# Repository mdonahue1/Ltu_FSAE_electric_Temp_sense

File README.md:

# Ltu_FSAE_electric_Temp_sense
temp sense board I developed in my 3 semesters in the LTU FSAE Electric competition.

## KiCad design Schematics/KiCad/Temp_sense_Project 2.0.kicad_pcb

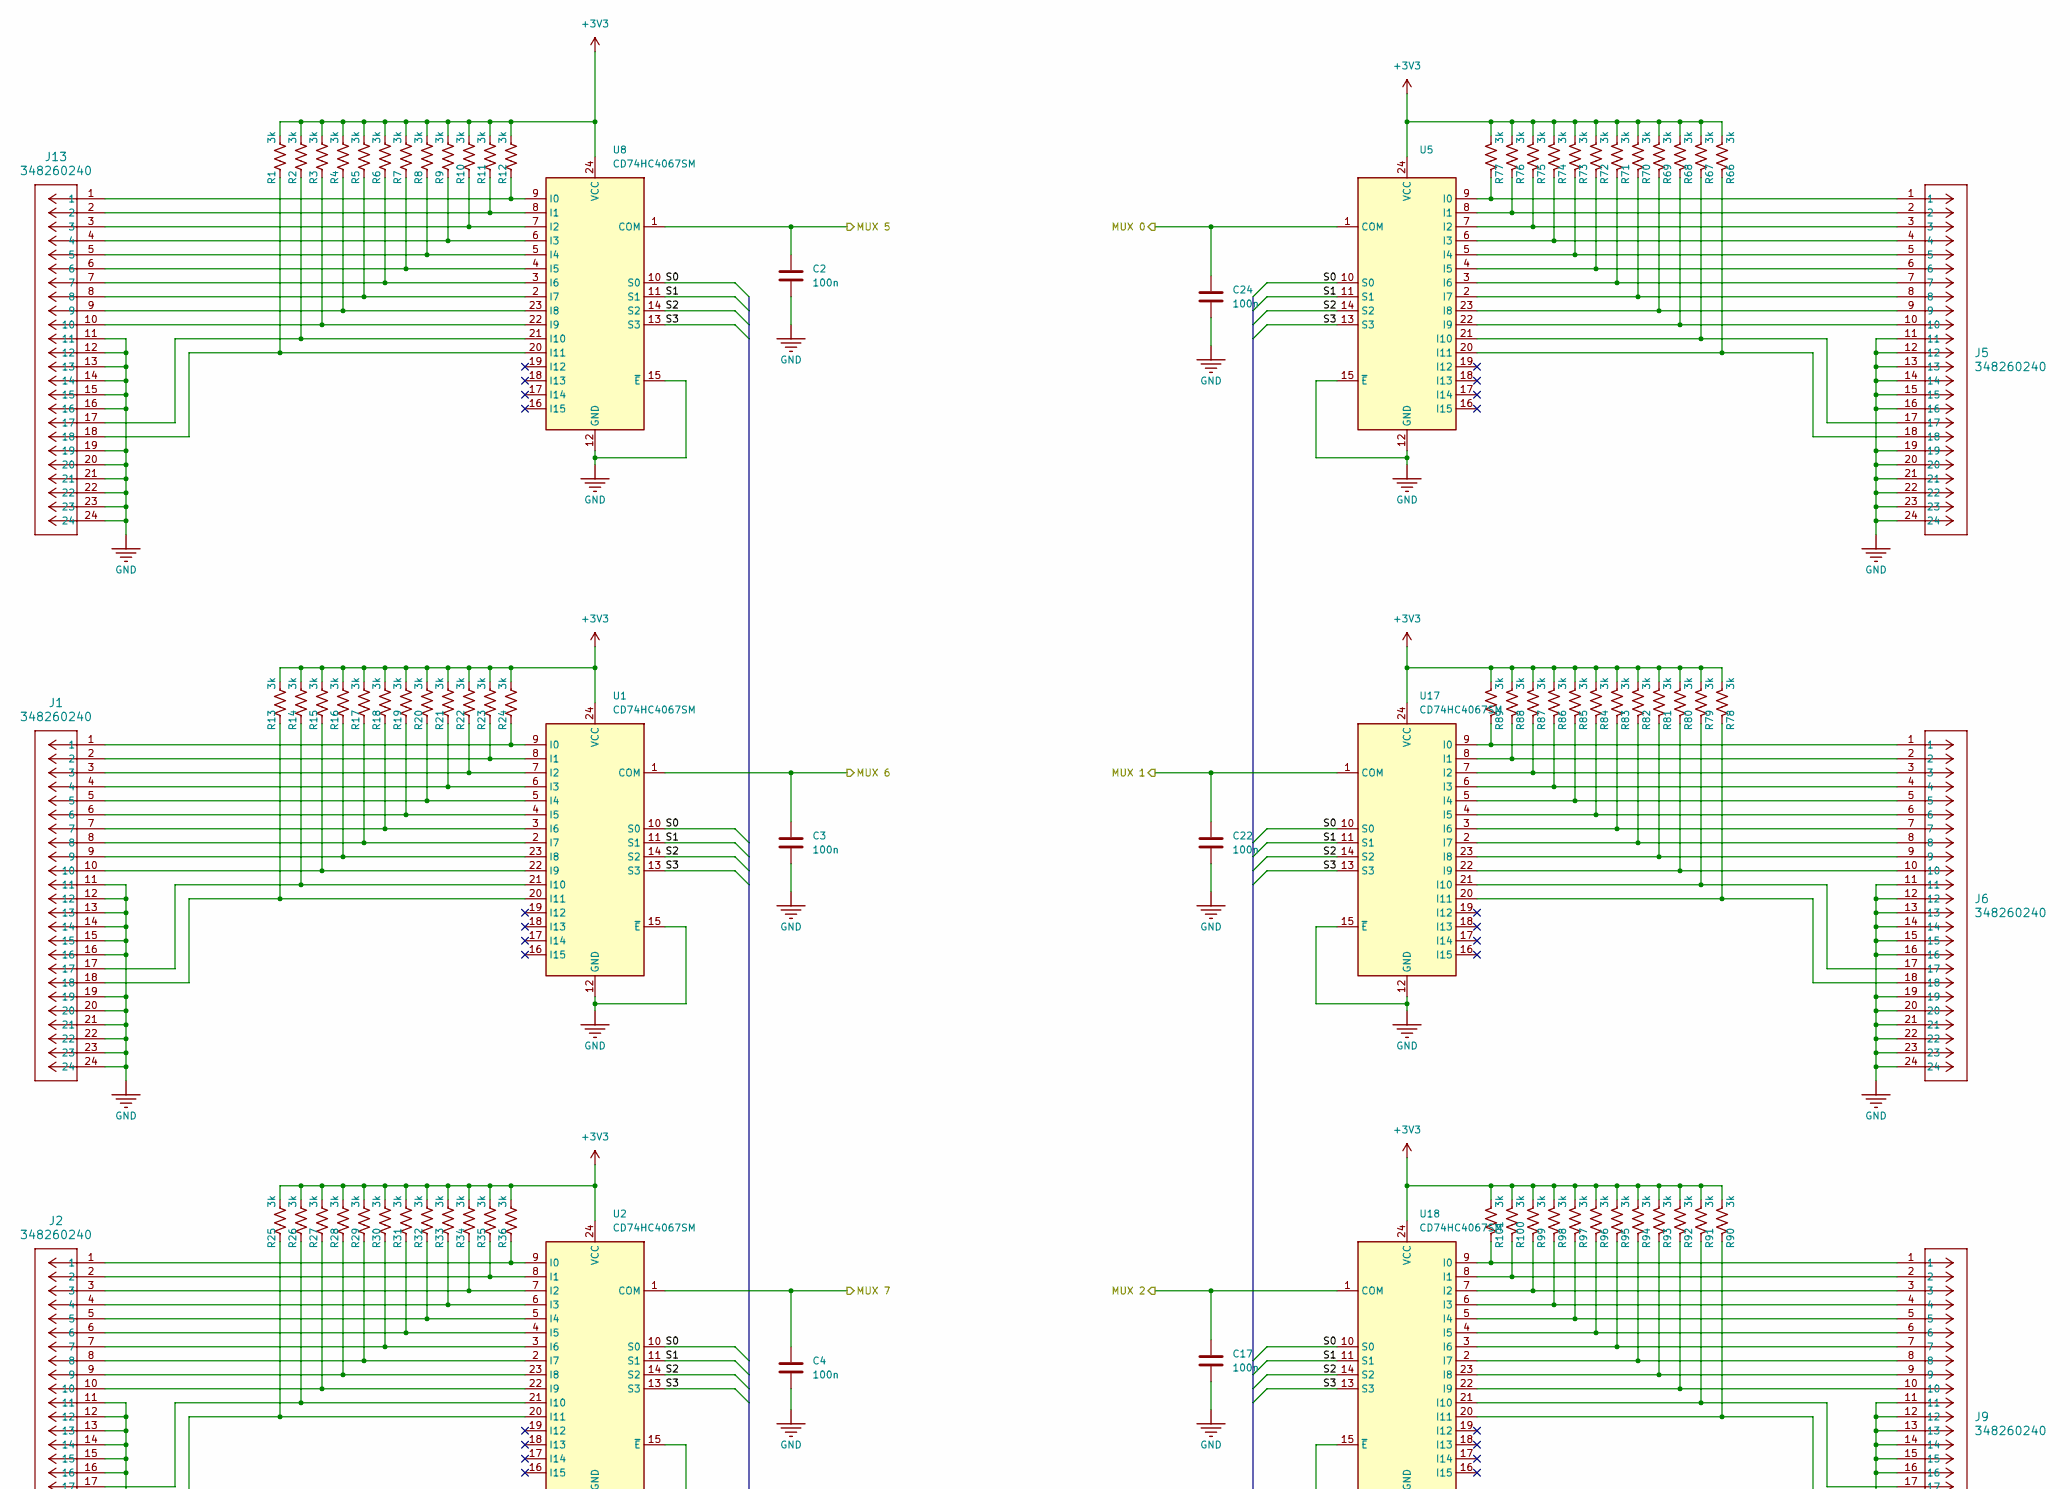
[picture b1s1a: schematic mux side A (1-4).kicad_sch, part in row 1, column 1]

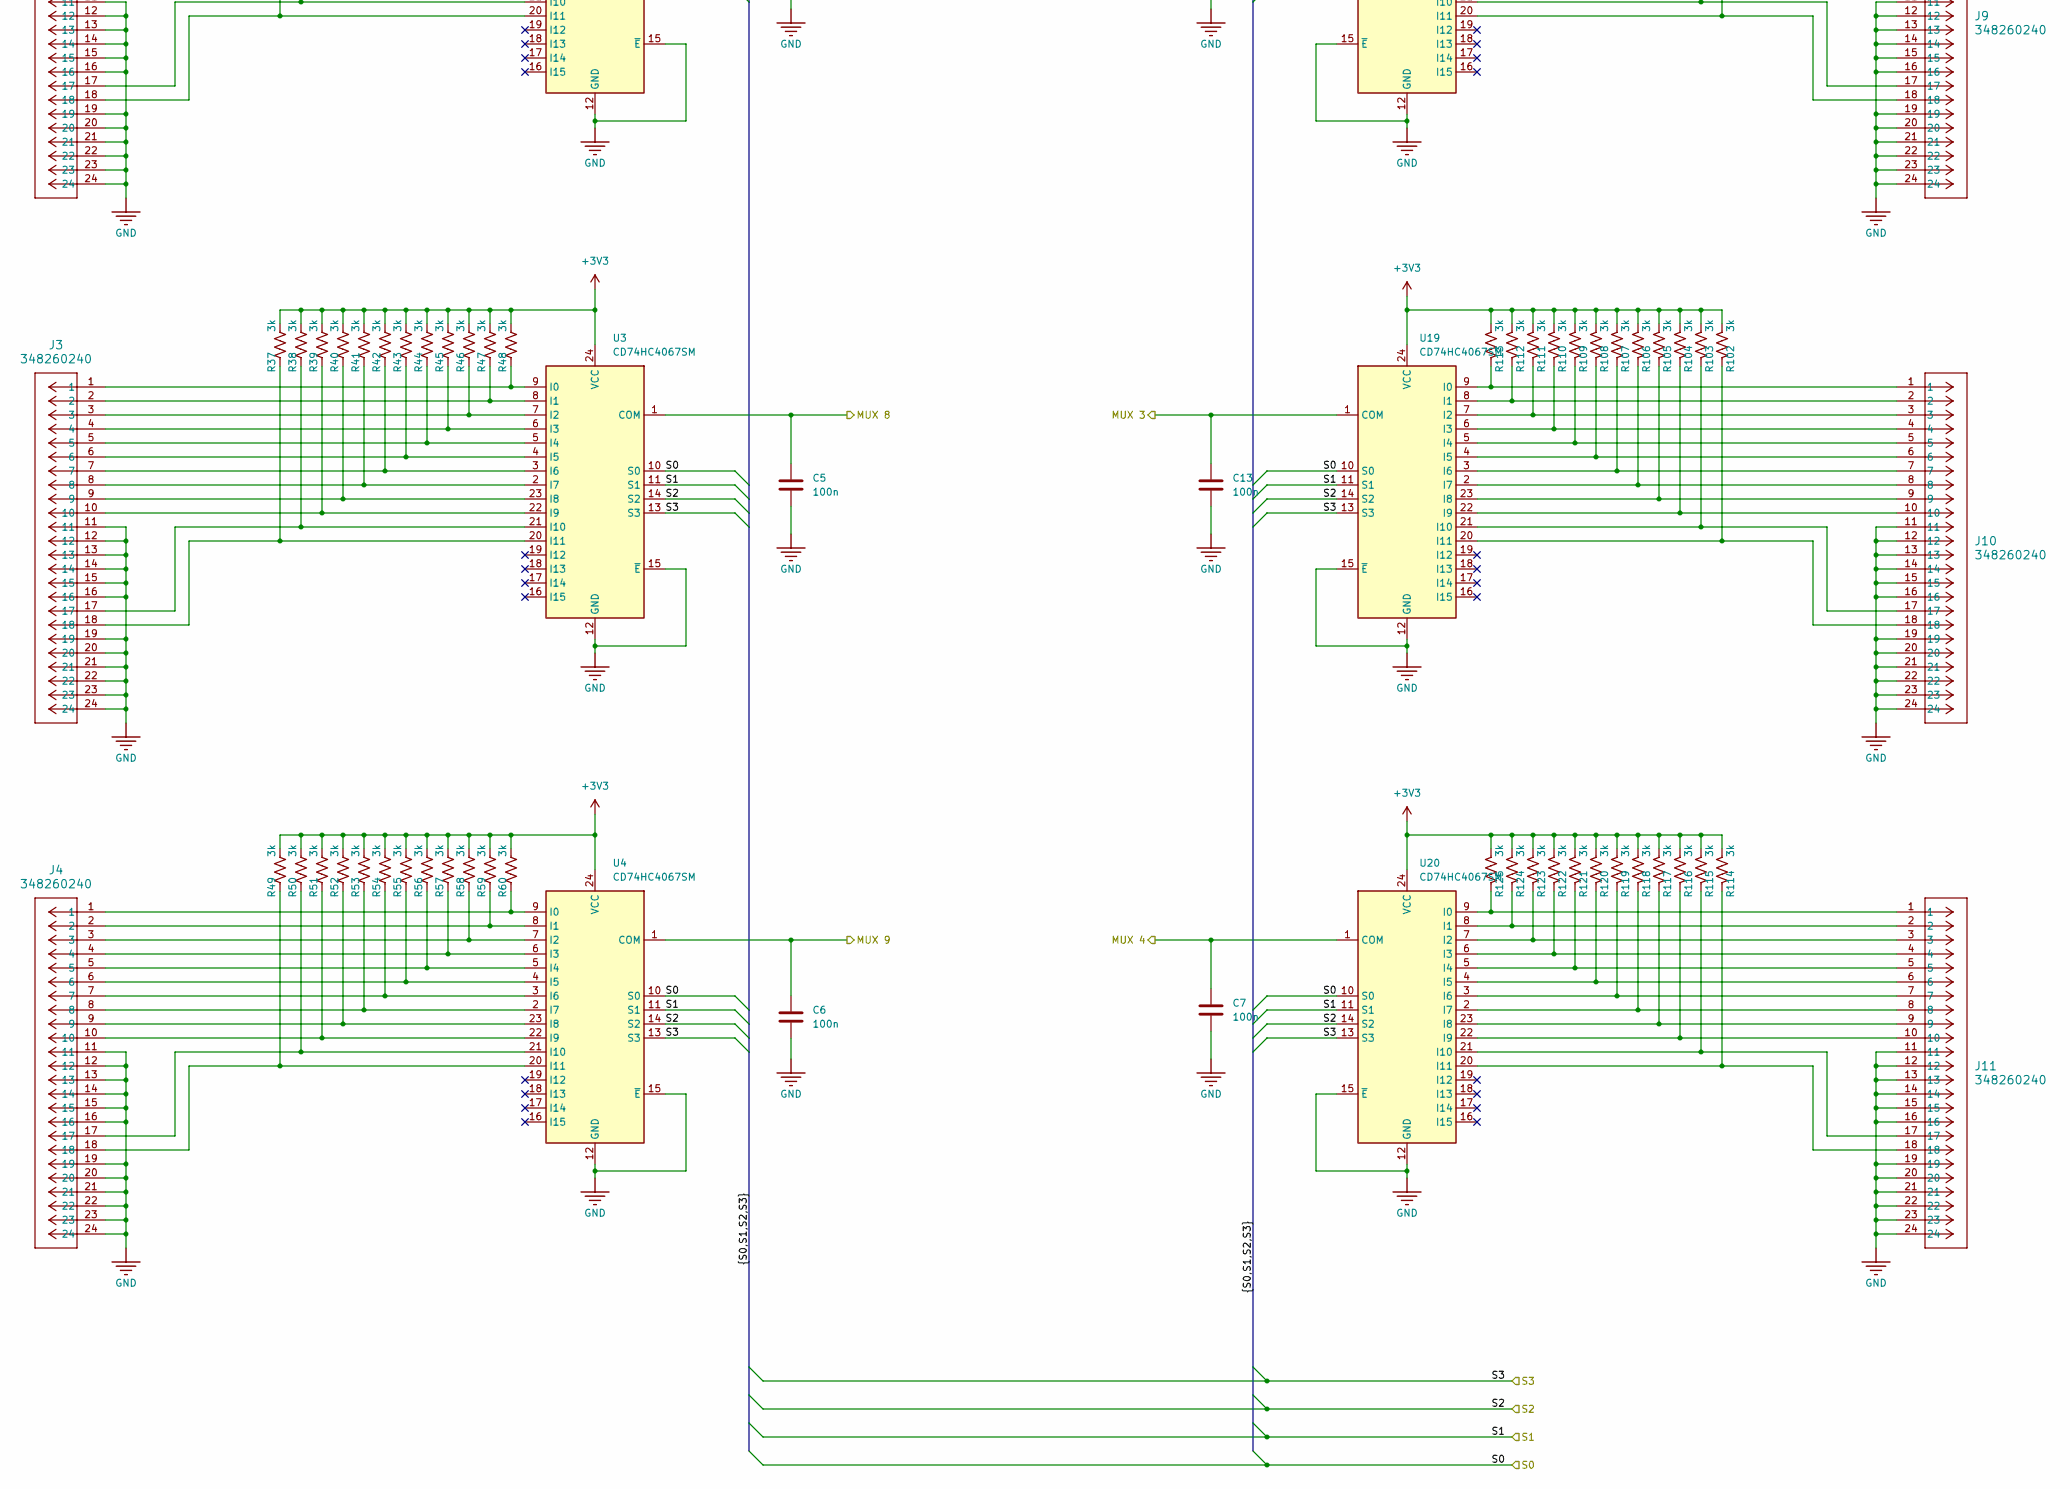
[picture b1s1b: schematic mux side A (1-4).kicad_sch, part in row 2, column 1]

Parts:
C2, C3, C4, C5, C6, C7, C13, C17, C22, C24: 100n; C_0603_1608Metric
J1, J2, J3, J4, J5, J6, J9, J10, J11, J13: 348260240; CONN_SD-34826-001_24_MOL
R1, R2, R3, R4, R5, R6, R7, R8, R9, R10, R11, R12, R13, R14, R15, R16, R17, R18, R19, R20, R21, R22, R23, R24, R25, R26, R27, R28, R29, R30, R31, R32, R33, R34, R35, R36, R37, R38, R39, R40, R41, R42, R43, R44, R45, R46, R47, R48, R49, R50, R51, R52, R53, R54, R55, R56, R57, R58, R59, R60, R66, R67, R68, R69, R70, R71, R72, R73, R74, R75, R76, R77, R78, R79, R80, R81, R82, R83, R84, R85, R86, R87, R88, R89, R90, R91, R92, R93, R94, R95, R96, R97, R98, R99, R100, R101, R102, R103, R104, R105, R106, R107, R108, R109, R110, R111, R112, R113, R114, R115, R116, R117, R118, R119, R120, R121, R122, R123, R124, R125: 3k; R_0603_1608Metric
U1, U2, U3, U4, U5, U8, U17, U18, U19, U20: CD74HC4067SM; SSOP-24_5.3x8.2mm_P0.65mm

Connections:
+3V3: R1.1, R2.1, R3.1, R4.1, R5.1, R6.1, R7.1, R8.1, R9.1, R10.1, R11.1, R12.1, R13.1, R14.1, R15.1, R16.1, R17.1, R18.1, R19.1, R20.1, R21.1, R22.1, R23.1, R24.1, R25.1, R26.1, R27.1, R28.1, R29.1, R30.1, R31.1, R32.1, R33.1, R34.1, R35.1, R36.1, R37.1, R38.1, R39.1, R40.1, R41.1, R42.1, R43.1, R44.1, R45.1, R46.1, R47.1, R48.1, R49.1, R50.1, R51.1, R52.1, R53.1, R54.1, R55.1, R56.1, R57.1, R58.1, R59.1, R60.1, R66.1, R67.1, R68.1, R69.1, R70.1, R71.1, R72.1, R73.1, R74.1, R75.1, R76.1, R77.1, R78.1, R79.1, R80.1, R81.1, R82.1, R83.1, R84.1, R85.1, R86.1, R87.1, R88.1, R89.1, R90.1, R91.1, R92.1, R93.1, R94.1, R95.1, R96.1, R97.1, R98.1, R99.1, R100.1, R101.1, R102.1, R103.1, R104.1, R105.1, R106.1, R107.1, R108.1, R109.1, R110.1, R111.1, R112.1, R113.1, R114.1, R115.1, R116.1, R117.1, R118.1, R119.1, R120.1, R121.1, R122.1, R123.1, R124.1, R125.1, U1.24 (VCC), U2.24 (VCC), U3.24 (VCC), U4.24 (VCC), U5.24 (VCC), U8.24 (VCC), U17.24 (VCC), U18.24 (VCC), U19.24 (VCC), U20.24 (VCC); also elsewhere on the board
/MCU/MUX 0: C24.1, U5.1 (COM); also elsewhere on the board
/MCU/MUX 1: C22.1, U17.1 (COM); also elsewhere on the board
/MCU/MUX 2: C17.1, U18.1 (COM); also elsewhere on the board
/MCU/MUX 3: C13.1, U19.1 (COM); also elsewhere on the board
/MCU/MUX 4: C7.1, U20.1 (COM); also elsewhere on the board
/MCU/MUX 5: C2.1, U8.1 (COM); also elsewhere on the board
/MCU/MUX 6: C3.1, U1.1 (COM); also elsewhere on the board
/MCU/MUX 7: C4.1, U2.1 (COM); also elsewhere on the board
/MCU/MUX 8: C5.1, U3.1 (COM); also elsewhere on the board
/MCU/MUX 9: C6.1, U4.1 (COM); also elsewhere on the board
/MCU/S0: U1.10 (S0), U2.10 (S0), U3.10 (S0), U4.10 (S0), U5.10 (S0), U8.10 (S0), U17.10 (S0), U18.10 (S0), U19.10 (S0), U20.10 (S0); also elsewhere on the board
/MCU/S1: U1.11 (S1), U2.11 (S1), U3.11 (S1), U4.11 (S1), U5.11 (S1), U8.11 (S1), U17.11 (S1), U18.11 (S1), U19.11 (S1), U20.11 (S1); also elsewhere on the board
/MCU/S2: U1.14 (S2), U2.14 (S2), U3.14 (S2), U4.14 (S2), U5.14 (S2), U8.14 (S2), U17.14 (S2), U18.14 (S2), U19.14 (S2), U20.14 (S2); also elsewhere on the board
/MCU/S3: U1.13 (S3), U2.13 (S3), U3.13 (S3), U4.13 (S3), U5.13 (S3), U8.13 (S3), U17.13 (S3), U18.13 (S3), U19.13 (S3), U20.13 (S3); also elsewhere on the board
GND: C2.2, C3.2, C4.2, C5.2, C6.2, C7.2, C13.2, C17.2, C22.2, C24.2, J1.11, J1.12, J1.13, J1.14, J1.15, J1.16, J1.19, J1.20, J1.21, J1.22, J1.23, J1.24, J2.11, J2.12, J2.13, J2.14, J2.15, J2.16, J2.19, J2.20, J2.21, J2.22, J2.23, J2.24, J3.11, J3.12, J3.13, J3.14, J3.15, J3.16, J3.19, J3.20, J3.21, J3.22, J3.23, J3.24, J4.11, J4.12, J4.13, J4.14, J4.15, J4.16, J4.19, J4.20, J4.21, J4.22, J4.23, J4.24, J5.11, J5.12, J5.13, J5.14, J5.15, J5.16, J5.19, J5.20, J5.21, J5.22, J5.23, J5.24, J6.11, J6.12, J6.13, J6.14, J6.15, J6.16, J6.19, J6.20, J6.21, J6.22, J6.23, J6.24, J9.11, J9.12, J9.13, J9.14, J9.15, J9.16, J9.19, J9.20, J9.21, J9.22, J9.23, J9.24, J10.11, J10.12, J10.13, J10.14, J10.15, J10.16, J10.19, J10.20, J10.21, J10.22, J10.23, J10.24, J11.11, J11.12, J11.13, J11.14, J11.15, J11.16, J11.19, J11.20, J11.21, J11.22, J11.23, J11.24, J13.11, J13.12, J13.13, J13.14, J13.15, J13.16, J13.19, J13.20, J13.21, J13.22, J13.23, J13.24, U1.12 (GND), U1.15 (~E), U2.12 (GND), U2.15 (~E), U3.12 (GND), U3.15 (~E), U4.12 (GND), U4.15 (~E), U5.12 (GND), U5.15 (~E), U8.12 (GND), U8.15 (~E), U17.12 (GND), U17.15 (~E), U18.12 (GND), U18.15 (~E), U19.12 (GND), U19.15 (~E), U20.12 (GND), U20.15 (~E); also elsewhere on the board
unnamed: J1.1, R24.2, U1.9 (I0)
unnamed: J1.2, R23.2, U1.8 (I1)
unnamed: J1.3, R22.2, U1.7 (I2)
unnamed: J1.4, R21.2, U1.6 (I3)
unnamed: J1.5, R20.2, U1.5 (I4)
unnamed: J1.6, R19.2, U1.4 (I5)
unnamed: J1.7, R18.2, U1.3 (I6)
unnamed: J1.8, R17.2, U1.2 (I7)
unnamed: J1.9, R16.2, U1.23 (I8)
unnamed: J1.10, R15.2, U1.22 (I9)
unnamed: J1.17, R14.2, U1.21 (I10)
unnamed: J1.18, R13.2, U1.20 (I11)
unnamed: J2.1, R36.2, U2.9 (I0)
unnamed: J2.2, R35.2, U2.8 (I1)
unnamed: J2.3, R34.2, U2.7 (I2)
unnamed: J2.4, R33.2, U2.6 (I3)
unnamed: J2.5, R32.2, U2.5 (I4)
unnamed: J2.6, R31.2, U2.4 (I5)
unnamed: J2.7, R30.2, U2.3 (I6)
unnamed: J2.8, R29.2, U2.2 (I7)
unnamed: J2.9, R28.2, U2.23 (I8)
unnamed: J2.10, R27.2, U2.22 (I9)
unnamed: J2.17, R26.2, U2.21 (I10)
unnamed: J2.18, R25.2, U2.20 (I11)
unnamed: J3.1, R48.2, U3.9 (I0)
unnamed: J3.2, R47.2, U3.8 (I1)
unnamed: J3.3, R46.2, U3.7 (I2)
unnamed: J3.4, R45.2, U3.6 (I3)
unnamed: J3.5, R44.2, U3.5 (I4)
unnamed: J3.6, R43.2, U3.4 (I5)
unnamed: J3.7, R42.2, U3.3 (I6)
unnamed: J3.8, R41.2, U3.2 (I7)
unnamed: J3.9, R40.2, U3.23 (I8)
unnamed: J3.10, R39.2, U3.22 (I9)
unnamed: J3.17, R38.2, U3.21 (I10)
unnamed: J3.18, R37.2, U3.20 (I11)
unnamed: J4.1, R60.2, U4.9 (I0)
unnamed: J4.2, R59.2, U4.8 (I1)
unnamed: J4.3, R58.2, U4.7 (I2)
unnamed: J4.4, R57.2, U4.6 (I3)
unnamed: J4.5, R56.2, U4.5 (I4)
unnamed: J4.6, R55.2, U4.4 (I5)
unnamed: J4.7, R54.2, U4.3 (I6)
unnamed: J4.8, R53.2, U4.2 (I7)
unnamed: J4.9, R52.2, U4.23 (I8)
unnamed: J4.10, R51.2, U4.22 (I9)
unnamed: J4.17, R50.2, U4.21 (I10)
unnamed: J4.18, R49.2, U4.20 (I11)
unnamed: J5.1, R77.2, U5.9 (I0)
unnamed: J5.2, R76.2, U5.8 (I1)
unnamed: J5.3, R75.2, U5.7 (I2)
unnamed: J5.4, R74.2, U5.6 (I3)
unnamed: J5.5, R73.2, U5.5 (I4)
unnamed: J5.6, R72.2, U5.4 (I5)
unnamed: J5.7, R71.2, U5.3 (I6)
unnamed: J5.8, R70.2, U5.2 (I7)
unnamed: J5.9, R69.2, U5.23 (I8)
unnamed: J5.10, R68.2, U5.22 (I9)
unnamed: J5.17, R67.2, U5.21 (I10)
unnamed: J5.18, R66.2, U5.20 (I11)
unnamed: J13.1, R12.2, U8.9 (I0)
unnamed: J13.2, R11.2, U8.8 (I1)
unnamed: J13.3, R10.2, U8.7 (I2)
unnamed: J13.4, R9.2, U8.6 (I3)
unnamed: J13.5, R8.2, U8.5 (I4)
unnamed: J13.6, R7.2, U8.4 (I5)
unnamed: J13.7, R6.2, U8.3 (I6)
unnamed: J13.8, R5.2, U8.2 (I7)
unnamed: J13.9, R4.2, U8.23 (I8)
unnamed: J13.10, R3.2, U8.22 (I9)
unnamed: J13.17, R2.2, U8.21 (I10)
unnamed: J13.18, R1.2, U8.20 (I11)
unnamed: J6.1, R89.2, U17.9 (I0)
unnamed: J6.2, R88.2, U17.8 (I1)
unnamed: J6.3, R87.2, U17.7 (I2)
unnamed: J6.4, R86.2, U17.6 (I3)
unnamed: J6.5, R85.2, U17.5 (I4)
unnamed: J6.6, R84.2, U17.4 (I5)
unnamed: J6.7, R83.2, U17.3 (I6)
unnamed: J6.8, R82.2, U17.2 (I7)
unnamed: J6.9, R81.2, U17.23 (I8)
unnamed: J6.10, R80.2, U17.22 (I9)
unnamed: J6.17, R79.2, U17.21 (I10)
unnamed: J6.18, R78.2, U17.20 (I11)
unnamed: J9.1, R101.2, U18.9 (I0)
unnamed: J9.2, R100.2, U18.8 (I1)
unnamed: J9.3, R99.2, U18.7 (I2)
unnamed: J9.4, R98.2, U18.6 (I3)
unnamed: J9.5, R97.2, U18.5 (I4)
unnamed: J9.6, R96.2, U18.4 (I5)
unnamed: J9.7, R95.2, U18.3 (I6)
unnamed: J9.8, R94.2, U18.2 (I7)
unnamed: J9.9, R93.2, U18.23 (I8)
unnamed: J9.10, R92.2, U18.22 (I9)
unnamed: J9.17, R91.2, U18.21 (I10)
unnamed: J9.18, R90.2, U18.20 (I11)
unnamed: J10.1, R113.2, U19.9 (I0)
unnamed: J10.2, R112.2, U19.8 (I1)
unnamed: J10.3, R111.2, U19.7 (I2)
unnamed: J10.4, R110.2, U19.6 (I3)
unnamed: J10.5, R109.2, U19.5 (I4)
unnamed: J10.6, R108.2, U19.4 (I5)
unnamed: J10.7, R107.2, U19.3 (I6)
unnamed: J10.8, R106.2, U19.2 (I7)
unnamed: J10.9, R105.2, U19.23 (I8)
unnamed: J10.10, R104.2, U19.22 (I9)
unnamed: J10.17, R103.2, U19.21 (I10)
unnamed: J10.18, R102.2, U19.20 (I11)
unnamed: J11.1, R125.2, U20.9 (I0)
unnamed: J11.2, R124.2, U20.8 (I1)
unnamed: J11.3, R123.2, U20.7 (I2)
unnamed: J11.4, R122.2, U20.6 (I3)
unnamed: J11.5, R121.2, U20.5 (I4)
unnamed: J11.6, R120.2, U20.4 (I5)
unnamed: J11.7, R119.2, U20.3 (I6)
unnamed: J11.8, R118.2, U20.2 (I7)
unnamed: J11.9, R117.2, U20.23 (I8)
unnamed: J11.10, R116.2, U20.22 (I9)
unnamed: J11.17, R115.2, U20.21 (I10)
unnamed: J11.18, R114.2, U20.20 (I11)

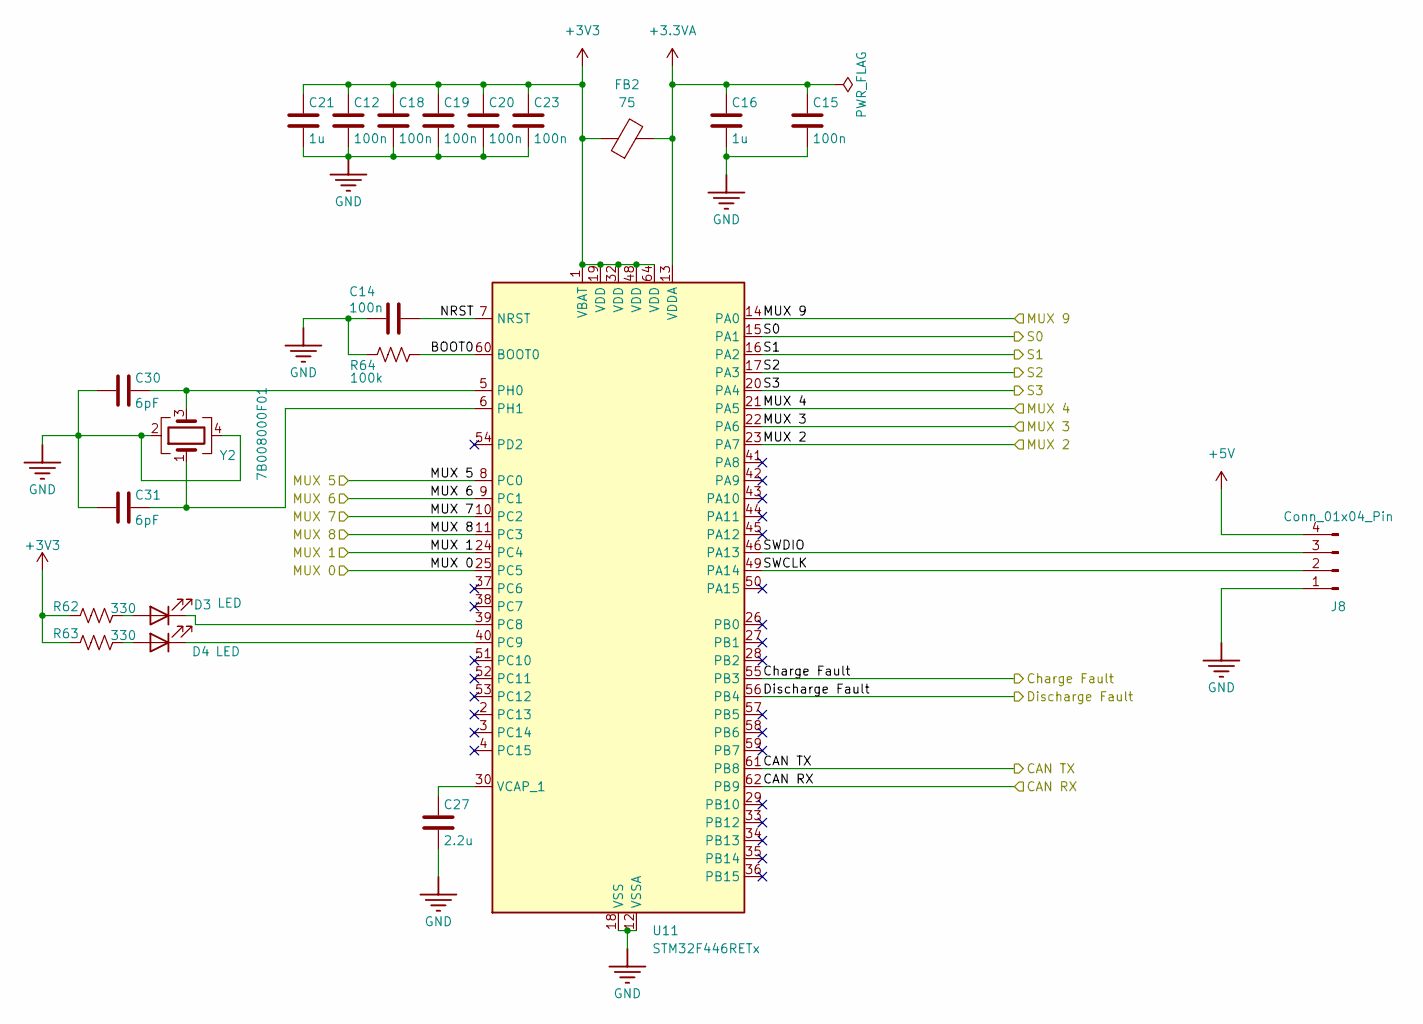
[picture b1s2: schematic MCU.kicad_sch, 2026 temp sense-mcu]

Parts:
C12, C14, C15, C18, C19, C20, C23: 100n; C_0603_1608Metric
C16, C21: 1u; C_0603_1608Metric
C27: 2.2u; C_0603_1608Metric
C30, C31: 6pF; C_0402_1005Metric; MPN GJM1555C1H6R0CB01D; JLCPCB Part # C161330
D3, D4: LED; LED_0603_1608Metric
FB2: 75; R_0603_1608Metric
J8: Conn_01x04_Pin; PinHeader_1x04_P2.54mm_Vertical
R62, R63: 330; R_0603_1608Metric
R64: 100k; R_0603_1608Metric
U11: STM32F446RETx; LQFP-64_10x10mm_P0.5mm
Y2: 7B008000F01; Crystal_SMD_3225-4Pin_3.2x2.5mm; MPN 7B008000F01; JLCPCB Part # C648984

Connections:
+3.3VA: C15.1, C16.1, FB2.2, U11.13 (VDDA)
+3V3: C12.1, C18.1, C19.1, C20.1, C21.1, C23.1, FB2.1, R62.1, R63.1, U11.1 (VBAT), U11.19 (VDD), U11.32 (VDD), U11.48 (VDD), U11.64 (VDD); also elsewhere on the board
+5V: J8.4; also elsewhere on the board
/MCU/BOOT0: R64.1, U11.60 (BOOT0)
/MCU/CAN RX: U11.62 (PB9); also elsewhere on the board
/MCU/CAN TX: U11.61 (PB8); also elsewhere on the board
/MCU/Charge Fault: U11.55 (PB3); also elsewhere on the board
/MCU/Discharge Fault: U11.56 (PB4); also elsewhere on the board
/MCU/MUX 0: U11.25 (PC5); also elsewhere on the board
/MCU/MUX 1: U11.24 (PC4); also elsewhere on the board
/MCU/MUX 2: U11.23 (PA7); also elsewhere on the board
/MCU/MUX 3: U11.22 (PA6); also elsewhere on the board
/MCU/MUX 4: U11.21 (PA5); also elsewhere on the board
/MCU/MUX 5: U11.8 (PC0); also elsewhere on the board
/MCU/MUX 6: U11.9 (PC1); also elsewhere on the board
/MCU/MUX 7: U11.10 (PC2); also elsewhere on the board
/MCU/MUX 8: U11.11 (PC3); also elsewhere on the board
/MCU/MUX 9: U11.14 (PA0); also elsewhere on the board
/MCU/NRST: C14.1, U11.7 (NRST)
/MCU/S0: U11.15 (PA1); also elsewhere on the board
/MCU/S1: U11.16 (PA2); also elsewhere on the board
/MCU/S2: U11.17 (PA3); also elsewhere on the board
/MCU/S3: U11.20 (PA4); also elsewhere on the board
/MCU/SWCLK: J8.2, U11.49 (PA14)
/MCU/SWDIO: J8.3, U11.46 (PA13)
GND: C12.2, C14.2, C15.2, C16.2, C18.2, C19.2, C20.2, C21.2, C23.2, C27.2, C30.2, C31.2, J8.1, R64.2, U11.12 (VSSA), U11.18 (VSS), U11.31 (VSS), U11.47 (VSS), U11.63 (VSS), Y2.2, Y2.4; also elsewhere on the board
unnamed: D3.2 (A), R62.2
unnamed: D3.1 (K), U11.39 (PC8)
unnamed: D4.2 (A), R63.2
unnamed: D4.1 (K), U11.40 (PC9)
unnamed: C30.1, U11.5 (PH0), Y2.3
unnamed: C31.1, U11.6 (PH1), Y2.1
unnamed: C27.1, U11.30 (VCAP_1)

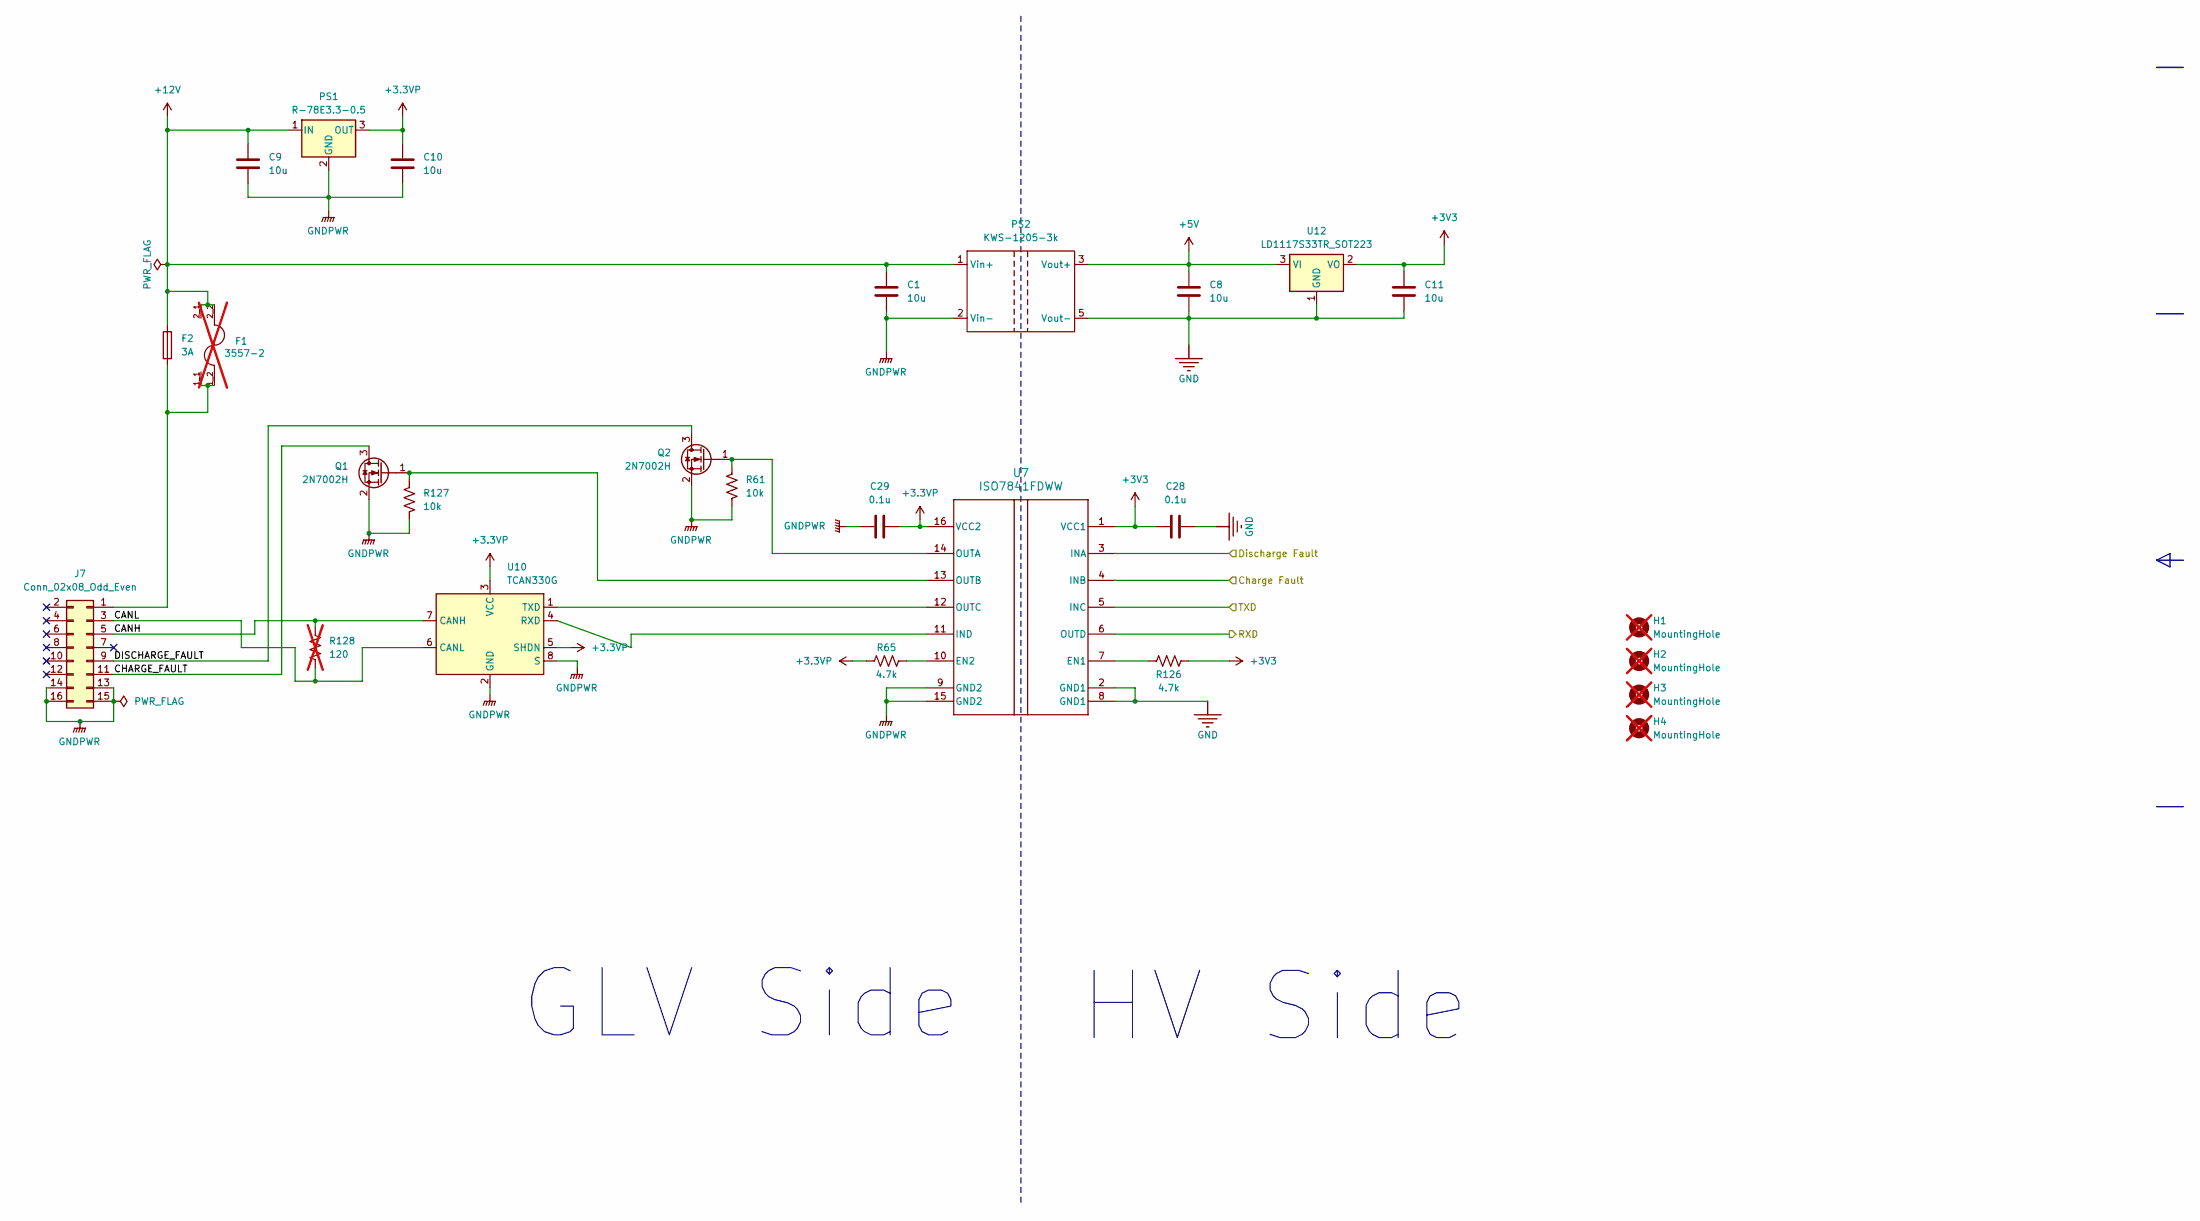
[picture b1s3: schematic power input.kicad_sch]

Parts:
C1, C8, C9, C10, C11: 10u; C_0603_1608Metric
C28, C29: 0.1u; C_0603_1608Metric
F1: 3557-2; FUSE_3557-2; PARTREV D; not fitted
F2: 3A; Fuse_0603_1608Metric; MPN SF-0603S300-2
H1, H2, H3, H4: MountingHole; MountingHole_6.4mm_M6; not fitted
J7: Conn_02x08_Odd_Even; PinSocket_2x08_P2.00mm_Vertical; MPN B16B-PHDSS
PS1: R-78E3.3-0.5; Converter_DCDC_RECOM_R-78E-0.5_THT
PS2: KWS-1205-3k; KWS-1205-3K
Q1, Q2: 2N7002H; SOT-23
R61, R127: 10k; R_0603_1608Metric
R65, R126: 4.7k; R_0603_1608Metric
R128: 120; R_0603_1608Metric; not fitted
U7: ISO7841FDWW; DWW0016A_N; MPN ISO7841FDWW
U10: TCAN330G
U12: LD1117S33TR_SOT223; SOT-223-3_TabPin2

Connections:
+3.3VP: C10.1, C29.1, PS1.3 (OUT), R65.1, U7.16 (VCC2), U10.3 (VCC), U10.5 (SHDN)
+3V3: C11.1, C28.1, R126.2, U7.1 (VCC1), U12.2 (VO); also elsewhere on the board
+5V: C8.1, PS2.3 (Vout+), U12.3 (VI); also elsewhere on the board
+12V: C1.1, C9.1, F1.2_1, F1.2_2, F2.1, PS1.1 (IN), PS2.1 (Vin+)
/MCU/CAN RX: U7.6 (OUTD); also elsewhere on the board
/MCU/CAN TX: U7.5 (INC); also elsewhere on the board
/MCU/Charge Fault: U7.4 (INB); also elsewhere on the board
/MCU/Discharge Fault: U7.3 (INA); also elsewhere on the board
/Power and Isolation/CANH: J7.5, R128.1, U10.7 (CANH)
/Power and Isolation/CANL: J7.3, R128.2, U10.6 (CANL)
/Power and Isolation/CHARGE_FAULT: J7.11, Q1.3 (D)
/Power and Isolation/DISCHARGE_FAULT: J7.9, Q2.3 (D)
GND: C8.2, C11.2, C28.2, PS2.5 (Vout-), U7.2 (GND1), U7.8 (GND1), U12.1 (GND); also elsewhere on the board
GNDPWR: C1.2, C9.2, C10.2, C29.2, J7.13, J7.14, J7.15, J7.16, PS1.2 (GND), PS2.2 (Vin-), Q1.2 (S), Q2.2 (S), R61.2, R127.2, U7.9 (GND2), U7.15 (GND2), U10.2 (GND), U10.8 (S)
unnamed: F1.1_1, F1.1_2, F2.2, J7.1
unnamed: Q1.1 (G), R127.1, U7.13 (OUTB)
unnamed: Q2.1 (G), R61.1, U7.14 (OUTA)
unnamed: R126.1, U7.7 (EN1)
unnamed: R65.2, U7.10 (EN2)
unnamed: U7.11 (IND), U10.4 (RXD)
unnamed: U7.12 (OUTC), U10.1 (TXD)

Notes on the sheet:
GLV Side
HV Side

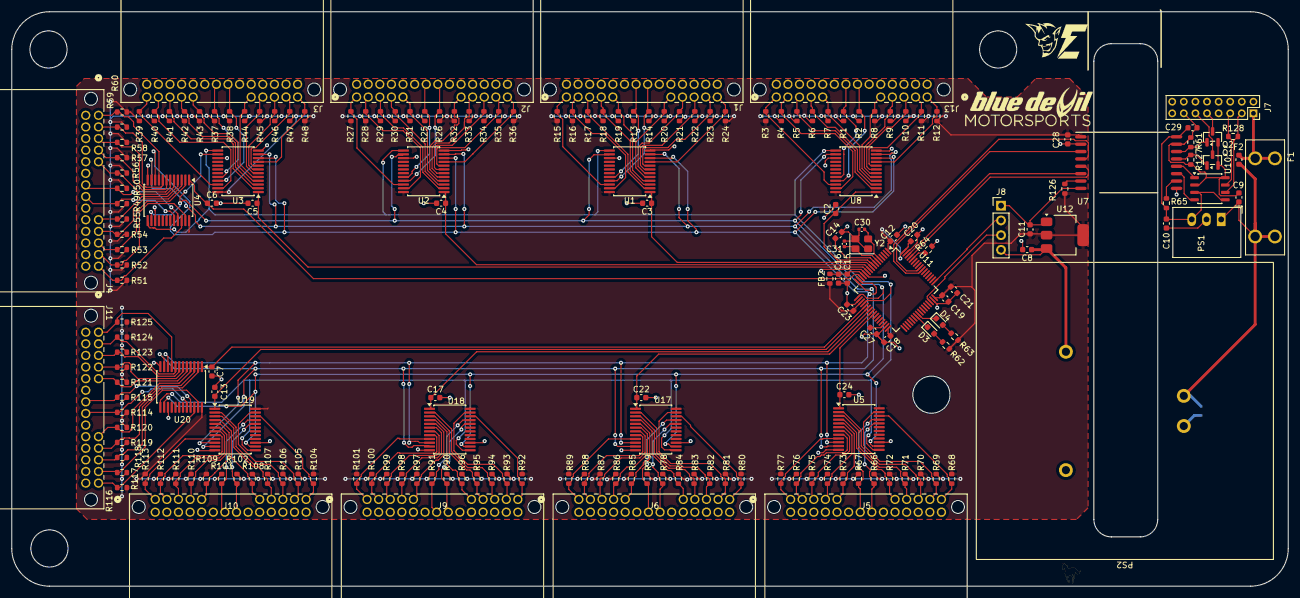
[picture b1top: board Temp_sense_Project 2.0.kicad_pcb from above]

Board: 2 copper layers, 220.0 x 99.0 mm, 197 parts (1 on the bottom side), 167 nets.

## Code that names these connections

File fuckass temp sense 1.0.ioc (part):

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Mcu.Name=STM32F446R(C-E)Tx
Mcu.Package=LQFP64
Mcu.UserName=STM32F446RETx
PA0-WKUP.GPIOParameters=GPIO_Label
PA0-WKUP.GPIO_Label=MUX 9
PA0-WKUP.Signal=ADCx_IN0
PA1.GPIOParameters=GPIO_Label
PA1.GPIO_Label=S0
PA1.Signal=GPIO_Output
PA13.Mode=Serial_Wire
PA13.Signal=SYS_JTMS-SWDIO
PA14.Mode=Serial_Wire
PA14.Signal=SYS_JTCK-SWCLK
PA2.GPIOParameters=GPIO_Label
PA2.GPIO_Label=S1
PA2.Signal=GPIO_Output
PA3.GPIOParameters=GPIO_Label
PA3.GPIO_Label=S2
PA3.Signal=GPIO_Output
PA4.GPIOParameters=GPIO_Label
PA4.GPIO_Label=S3
PA4.Signal=GPIO_Output
PA5.GPIOParameters=GPIO_Label
PA5.GPIO_Label=MUX 4
PA5.Signal=ADCx_IN5
PA6.GPIOParameters=GPIO_Label
PA6.GPIO_Label=MUX 3
PA6.Signal=ADCx_IN6
PA7.GPIOParameters=GPIO_Label
PA7.GPIO_Label=MUX 2
PA7.Signal=ADCx_IN7
PB3.GPIOParameters=GPIO_Label
PB3.GPIO_Label=Charge Fault
PB3.Signal=GPIO_Output
PB4.GPIOParameters=GPIO_Label
PB4.GPIO_Label=Discharge Fault
PB4.Signal=GPIO_Output
PB8.Mode=CAN_Activate
PB8.Signal=CAN1_RX
PB9.Mode=CAN_Activate
PB9.Signal=CAN1_TX
PC0.GPIOParameters=GPIO_Label
PC0.GPIO_Label=MUX 5
PC0.Signal=ADCx_IN10
PC1.GPIOParameters=GPIO_Label
PC1.GPIO_Label=MUX 6
PC1.Signal=ADCx_IN11
PC2.GPIOParameters=GPIO_Label
PC2.GPIO_Label=MUX 7
PC2.Signal=ADCx_IN12
PC3.GPIOParameters=GPIO_Label
PC3.GPIO_Label=MUX 8
PC3.Signal=ADCx_IN13
PC4.GPIOParameters=GPIO_Label
PC4.GPIO_Label=MUX 1
PC4.Signal=ADCx_IN14
PC5.GPIOParameters=GPIO_Label
PC5.GPIO_Label=MUX 0
PC5.Signal=ADCx_IN15
PC8.GPIOParameters=GPIO_Label
PC8.GPIO_Label=Orange LED
PC8.Signal=GPIO_Output
PC9.GPIOParameters=GPIO_Label
PC9.GPIO_Label=Green LED
PC9.Signal=GPIO_Output
PH0-OSC_IN.Mode=HSE-External-Oscillator
PH0-OSC_IN.Signal=RCC_OSC_IN
PH1-OSC_OUT.Mode=HSE-External-Oscillator
PH1-OSC_OUT.Signal=RCC_OSC_OUT
RCC.HSE_VALUE=8000000
RCC.SYSCLKFreq_VALUE=180000000
RCC.SYSCLKSource=RCC_SYSCLKSOURCE_PLLCLK
board=custom

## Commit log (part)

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2025-09-16 Batman commit (has no parents)
2025-11-30 Add files via upload
    most recent coding changes as of 11/30/2025
2025-11-30 Add files via upload
    I think i may have forgotten these for most recent upload
2026-01-27 Add files via upload
    temp sense board project as of 1/20/26
2026-02-05 Add files via upload
    temp sense as of 2-5-26
2026-03-10 THE CODE
    THANK YOU
2026-03-10 Wrap up initial code for temp sense
2026-03-10 Remove binary outputs from tracking
2026-03-10 Add KiCad Schematics. Clean up misc stuff.
2026-03-10 Let it rip over can
2026-03-11 Fix all errors and warnings
2026-03-11 Start peripherals correctly
2026-03-12 Fix a few bugs and start writing main temp sense logic
2026-03-12 Update schematics
2026-03-12 Update project launch settings
2026-03-12 Add test folder
2026-03-13 Unit test most of the core logic
2026-03-14 Add checks for minimum temperatures
2026-03-14 Remove build folder from tracking
2026-03-14 Add fault triggers for invalid readings
2026-03-14 Skip bad readings from stats in summary
2026-03-14 Connect temp sense core to hardware layer
2026-03-16 Condense layout to 2 layers
2026-03-17 More pcb layout work
2026-03-17 continued net work
    idk how tf kicad works hopefully we dont need all 30 files
2026-03-18 final routing finished added deftones icons
2026-03-18 pcb file changed to not error out kicad
    also finished a few routes I missed
2026-03-20 Get rid of excess files
2026-03-20 Move some silkscreen around
